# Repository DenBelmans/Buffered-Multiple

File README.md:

# Buffered-Multiple
A 2HP buffered Multiple in Eurorack format. 2x3 or 1x6 configurations possible.

***** Build Instructions *****

1) Start off by placing the right-angled headers in the PCB that will house the thonkiconns. Place their straight leads through the holes and cut them off flush with the PCB. Take them out again and cut them off a little more so that you can solder them flush to the board without any stubs sticking out. Solder them.
2) Place all thonkiconns on the board, place the front panel on and fasten the nuts. Then flip over the assembly and solder the jacks in place.
3) Take the smaller pcb and solder all resistors, diodes, capacitors and ferrite beads. Make sure you solder the electrolytic capacitors as flush as possible or if you are using caps that are taller than 5mm solder them with their bodies flat on the PCB.
4) Solder the IC's directly to the board. There is no room for sockets!
5) Place the second board on the right angled connectors so that the second board tilted a bit down (towards the side that has no components. Make sure you stay within the 2HP width! Then solder it in place.
6) Solder the 1x5 right angled power connector. I left room for a 2x5 connector but these were a little tall. I used the rowo furthest away from the edge. Solder it so that, when connected, the power connector is within the 2HP width.

That should be all. If you encounter any problems or have questions, feel free to contact me via e-mail: belmansander@gmail.com

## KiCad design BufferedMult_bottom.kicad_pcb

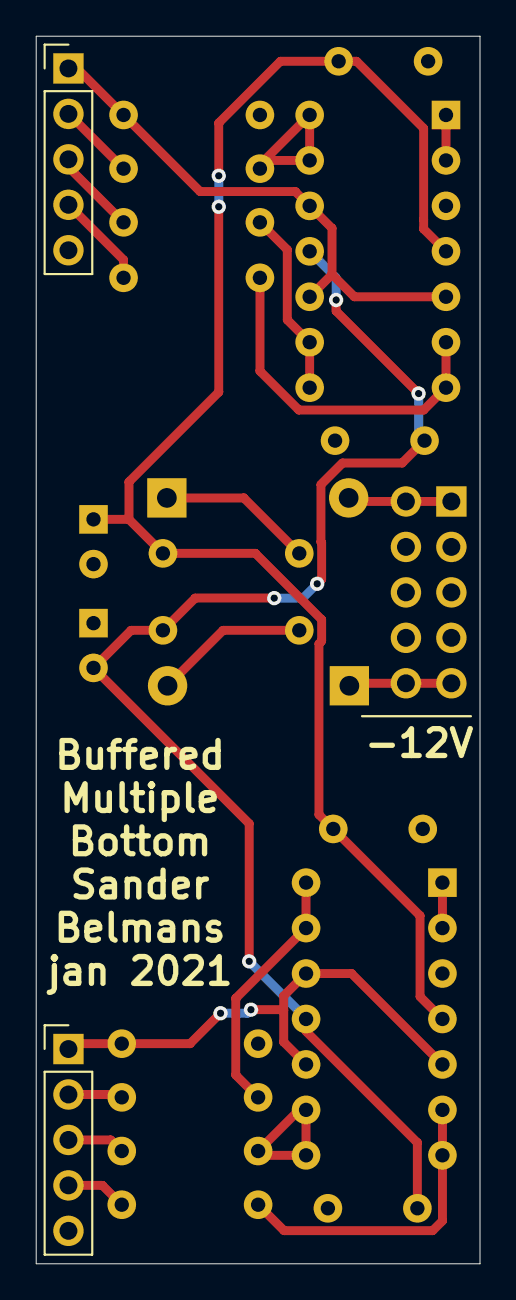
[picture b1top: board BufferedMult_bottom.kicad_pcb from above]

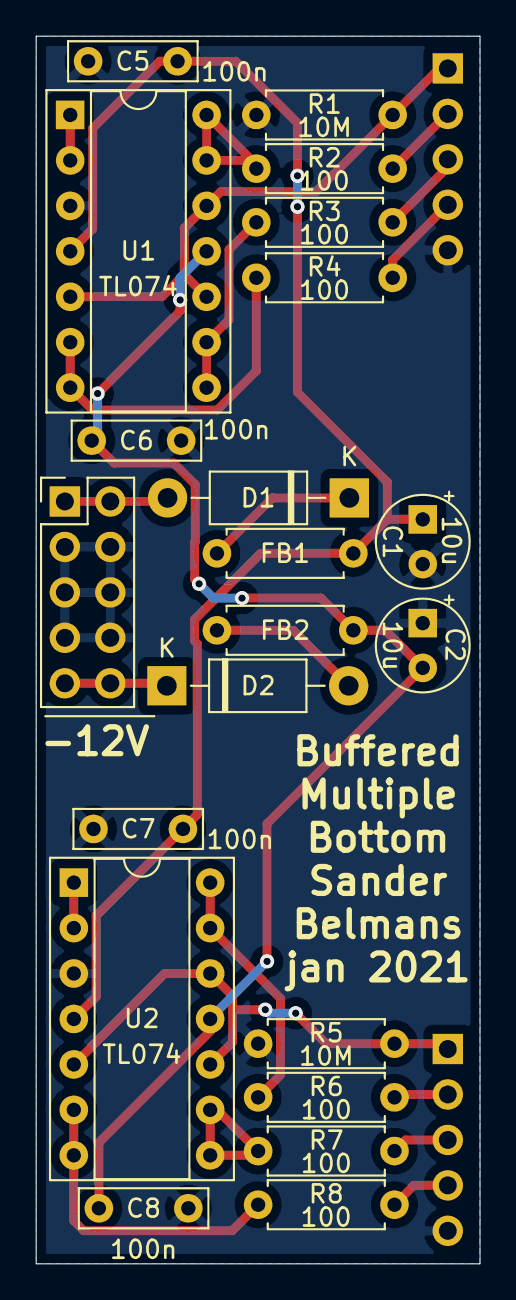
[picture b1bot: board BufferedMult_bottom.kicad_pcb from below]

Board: 2 copper layers, 24.8 x 68.6 mm, 23 parts (21 on the bottom side), 23 nets.

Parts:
C1, C2: 10u; CP_Radial_Tantal_D5.0mm_P2.50mm
C5, C6, C7, C8: 100n; C_Rect_L7.0mm_W2.0mm_P5.00mm
D1, D2: 1N5817; D_DO-41_SOD81_P10.16mm_Horizontal
FB1, FB2: Ferrite_Bead; R_Axial_DIN0207_L6.3mm_D2.5mm_P7.62mm_Horizontal
J1, J2: Conn_01x05_Male; PinHeader_1x05_P2.54mm_Vertical
J3: Conn_02x05_Odd_Even; PinHeader_2x05_P2.54mm_Vertical
R1, R5: 10M; R_Axial_DIN0207_L6.3mm_D2.5mm_P7.62mm_Horizontal
R2, R3, R4, R6, R7, R8: 100; R_Axial_DIN0207_L6.3mm_D2.5mm_P7.62mm_Horizontal
U1, U2: TL074; DIP-14_W7.62mm_Socket

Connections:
+12V: C1.1, C5.1, C7.1, FB1.2, U1.4, U2.4
-12V: C2.2, C6.2, C8.2, FB2.2, U1.11, U2.11
GND: C1.2, C2.1, C5.2, C6.1, C7.2, C8.1, J1.5, J2.5, J3.3, J3.4, J3.5, J3.6, J3.7, J3.8, R1.1, R5.1, U1.3, U2.3
unnamed: D1.1, FB1.1
unnamed: D1.2, J3.1, J3.2
unnamed: D2.1, J3.9, J3.10
unnamed: D2.2, FB2.1
unnamed: J1.1, R1.2, U1.5, U1.10, U1.12
unnamed: J1.2, R2.2
unnamed: J1.3, R3.2
unnamed: J1.4, R4.2
unnamed: J2.1, R5.2, U2.5, U2.10, U2.12
unnamed: J2.2, R6.2
unnamed: J2.3, R7.2
unnamed: J2.4, R8.2
unnamed: R2.1, U1.13, U1.14
unnamed: R3.1, U1.8, U1.9
unnamed: R4.1, U1.6, U1.7
unnamed: R6.1, U2.13, U2.14
unnamed: R7.1, U2.8, U2.9
unnamed: R8.1, U2.6, U2.7
unnamed: U1.1, U1.2
unnamed: U2.1, U2.2

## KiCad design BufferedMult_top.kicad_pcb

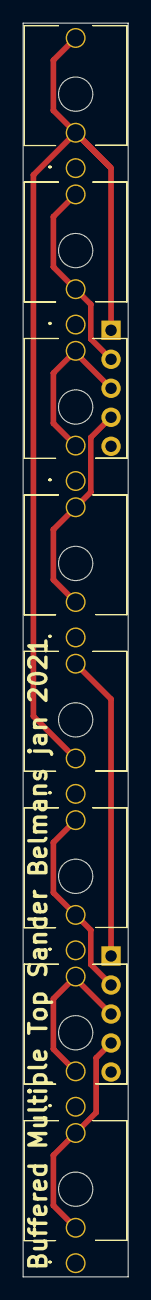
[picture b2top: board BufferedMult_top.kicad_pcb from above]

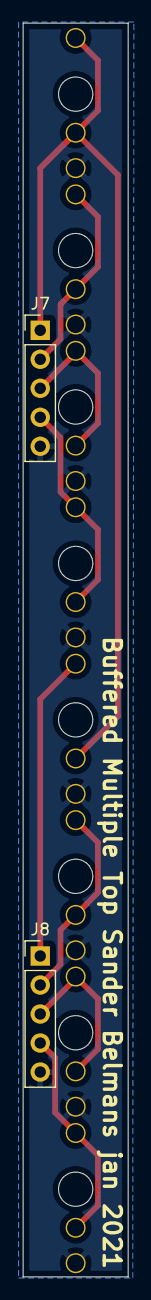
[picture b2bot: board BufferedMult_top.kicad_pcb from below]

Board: 2 copper layers, 9.2 x 109.8 mm, 10 parts (2 on the bottom side), 9 nets.

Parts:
INA1: AudioJack3; Thonkiconn
INB1: AudioJack3; Thonkiconn
J1, J2, J3, J4, J5, J6: AudioJack3; Thonkiconn
J7, J8: Conn_01x05_Male; PinHeader_1x05_P2.54mm_Vertical

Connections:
GND: INA1.S, INB1.S, J1.S, J2.S, J3.S, J4.S, J5.S, J6.S, J7.5, J8.5
unnamed: INA1.R, INA1.T, INB1.R, J7.1
unnamed: INB1.T, J8.1
unnamed: J1.R, J1.T, J7.2
unnamed: J2.R, J2.T, J7.3
unnamed: J3.R, J3.T, J7.4
unnamed: J4.R, J4.T, J8.2
unnamed: J5.R, J5.T, J8.3
unnamed: J6.R, J6.T, J8.4
